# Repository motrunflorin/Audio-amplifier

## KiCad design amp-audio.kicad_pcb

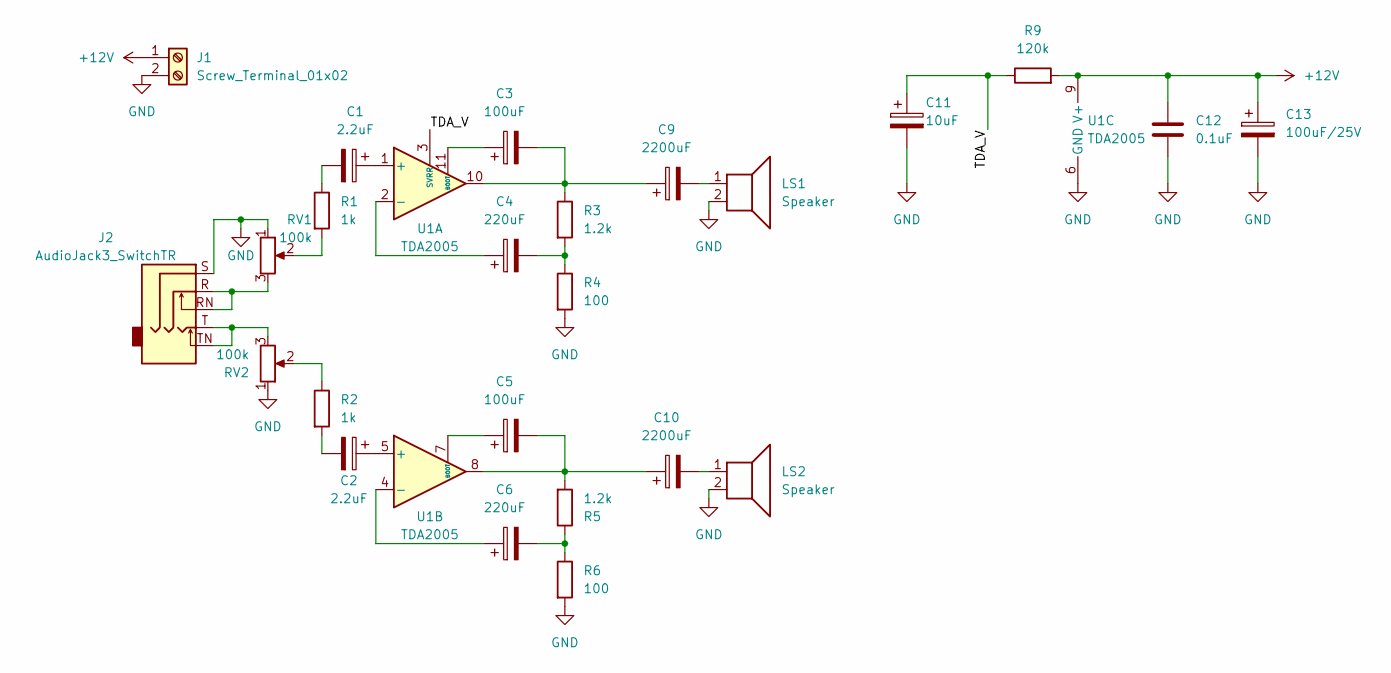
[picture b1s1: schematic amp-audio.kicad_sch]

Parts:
C1, C2: 2.2uF; CP_Radial_D5.0mm_P2.50mm
C3, C5: 100uF; CP_Radial_D6.3mm_P2.50mm
C4, C6: 220uF; CP_Radial_D6.3mm_P2.50mm
C9, C10: 2200uF; CP_Radial_D12.5mm_P5.00mm
C11: 10uF; CP_Radial_D5.0mm_P2.50mm
C12: 0.1uF; C_Disc_D8.0mm_W2.5mm_P5.00mm
C13: 100uF/25V; CP_Radial_D6.3mm_P2.50mm
J1: Screw_Terminal_01x02; PhoenixContact_MSTBA_2,5_2-G_1x02_P5.00mm_Horizontal
J2: AudioJack3_SwitchTR; Jack_3.5mm_CUI_SJ1-3525N_Horizontal
LS1, LS2: Speaker; PhoenixContact_MSTBA_2,5_2-G_1x02_P5.00mm_Horizontal
R1, R2: 1k; R_Axial_DIN0207_L6.3mm_D2.5mm_P7.62mm_Horizontal
R3, R5: 1.2k; R_Axial_DIN0204_L3.6mm_D1.6mm_P2.54mm_Vertical
R4: 100; R_Axial_DIN0204_L3.6mm_D1.6mm_P2.54mm_Vertical
R6: 100; R_Axial_DIN0207_L6.3mm_D2.5mm_P7.62mm_Horizontal
R9: 120k; R_Axial_DIN0207_L6.3mm_D2.5mm_P7.62mm_Horizontal
RV1, RV2: 100k; Potentiometer_Alps_RK163_Single_Horizontal
U1: TDA2005; TO-220-11_P3.4x5.08mm_StaggerOdd_Lead4.85mm_Vertical

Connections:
+12V: C12.1, C13.1, J1.1, R9.2, U1.9 (V+)
/TDA_V: C11.1, R9.1, U1.3 (SVRR)
GND: C11.2, C12.2, C13.2, J1.2, J2.S, LS1.2, LS2.2, R4.2, R6.2, RV1.1, RV2.1, U1.6 (GND)
unnamed: C1.2, R1.1
unnamed: C2.2, R2.2
unnamed: C3.2, C9.1, R3.1, U1.10
unnamed: C4.2, R3.2, R4.1
unnamed: C6.2, R5.1, R6.1
unnamed: C9.2, LS1.1
unnamed: C5.2, C10.1, R5.2, U1.8
unnamed: C10.2, LS2.1
unnamed: J2.R, J2.RN, RV1.3
unnamed: J2.T, J2.TN, RV2.3
unnamed: R1.2, RV1.2
unnamed: R2.1, RV2.2
unnamed: C1.1, U1.1 (+)
unnamed: C4.1, U1.2 (-)
unnamed: C3.1, U1.11 (BOOT)
unnamed: C2.1, U1.5 (+)
unnamed: C6.1, U1.4 (-)
unnamed: C5.1, U1.7 (BOOT)

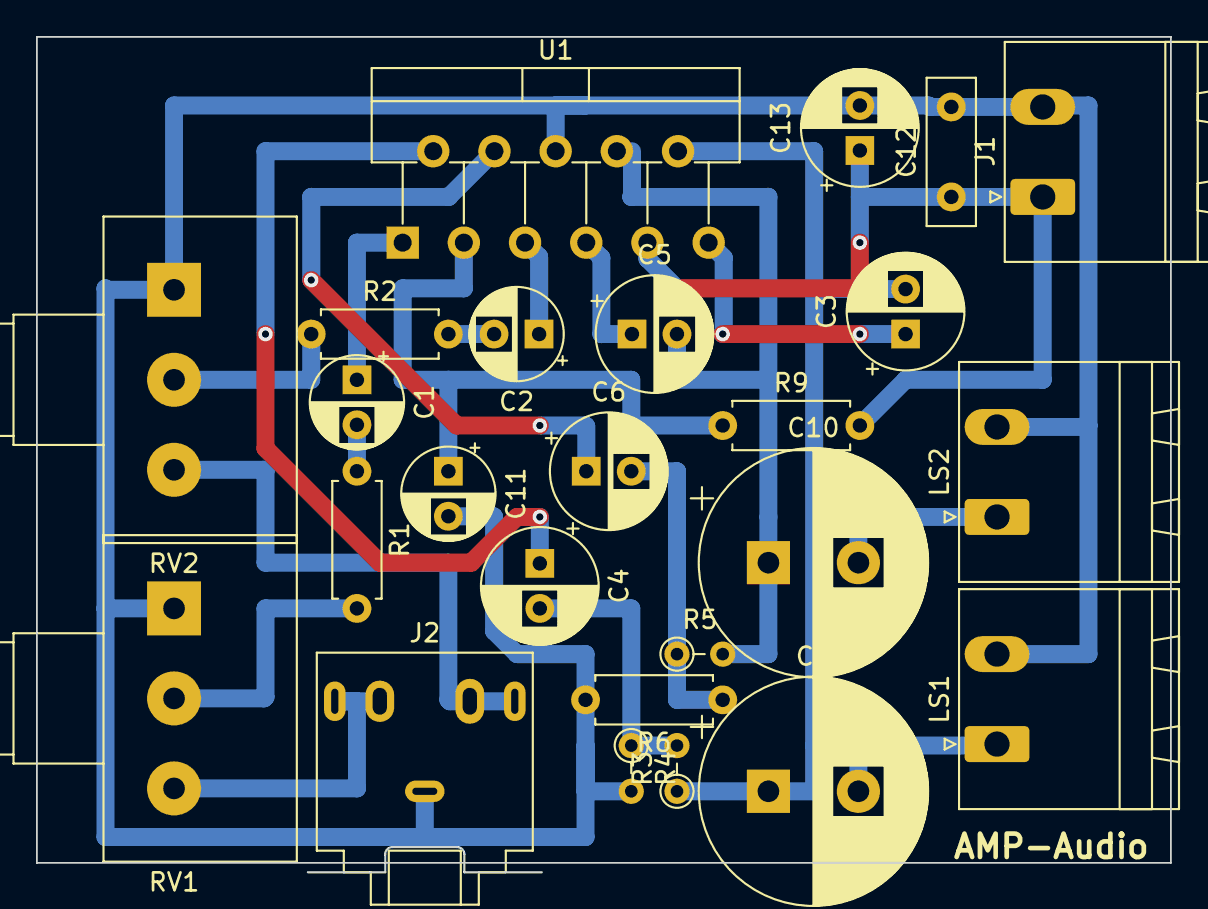
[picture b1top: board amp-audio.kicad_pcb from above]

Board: 2 copper layers, 63.0 x 46.4 mm, 25 parts (0 on the bottom side), 21 nets.

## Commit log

2025-02-28 Created using Colab
